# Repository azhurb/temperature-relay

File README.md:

# Smart outlet

Outlet controlled by a temperature sensor using *ATmega8-P*.  
The heater can be connected to the smart outlet and it will act as a thermostat.

## Demo

## License
Licensed under the MIT license.

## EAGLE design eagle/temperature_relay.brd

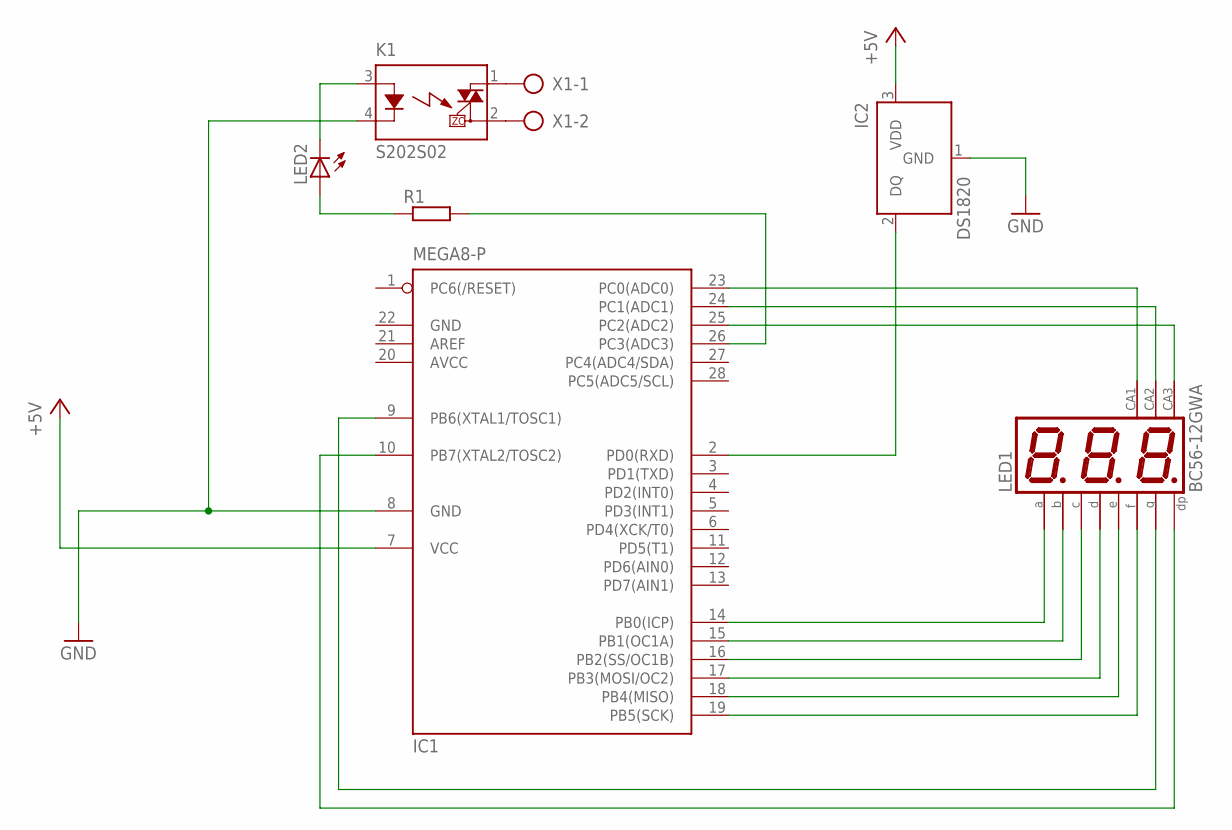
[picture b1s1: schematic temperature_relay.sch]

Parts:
IC1: MEGA8-P; DIL28-3
IC2: DS1820; TO-92
K1: S202S02
LED1: BC56-12GWA; BX56-12
LED2: LED5MM
R1: R-EU_0309/12; 0309/12
X1: AK300/2

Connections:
+5V: IC1.7 (VCC), IC2.3 (VDD)
AVCC: IC1.20 (AVCC)
GND: IC1.8 (GND), IC1.22 (GND), IC2.1 (GND), K1.4 (K)
unnamed: IC1.23 (PC0(ADC0)), LED1.12 (CA)
unnamed: IC1.24 (PC1(ADC1)), LED1.9 (CA)
unnamed: IC1.25 (PC2(ADC2)), LED1.8 (CA)
unnamed: IC1.14 (PB0(ICP)), LED1.11 (A)
unnamed: IC1.15 (PB1(OC1A)), LED1.7 (B)
unnamed: IC1.16 (PB2(SS/OC1B)), LED1.4 (C)
unnamed: IC1.17 (PB3(MOSI/OC2)), LED1.2 (D)
unnamed: IC1.18 (PB4(MISO)), LED1.1 (E)
unnamed: IC1.19 (PB5(SCK)), LED1.10 (F)
unnamed: IC1.9 (PB6(XTAL1/TOSC1)), LED1.5 (G)
unnamed: IC1.10 (PB7(XTAL2/TOSC2)), LED1.3 (DP)
unnamed: IC1.2 (PD0(RXD)), IC2.2 (DQ)
unnamed: IC1.26 (PC3(ADC3)), R1.2
unnamed: LED2.A, R1.1
unnamed: K1.3 (A), LED2.K (C)
unnamed: K1.2 (DS2), X1.2
unnamed: K1.1 (DS1), X1.1

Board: 2 copper layers, 7 parts (0 on the bottom side), 19 nets, no tracks yet.

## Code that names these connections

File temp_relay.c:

/***Использование динамической индикации***/
#include <avr/io.h>
#include <avr/interrupt.h>
#include <util/delay.h>

#include "delay.h"
#include "onewire.h"
#include "ds18x20.h"


char SEGMENT[ ] = {0x3F, 0x06, 0x5B, 0x4F, 0x66, 0x6D, 0x7D, 0x07, 0x7F, 0x6F};

volatile unsigned char segcounter = 0;
volatile int display1 = 0;

// Обработчик прерывания по переполнению таймера2
ISR (TIMER2_OVF_vect)
{    
	PORTB = 0x00; //гасим все разряды
	DDRC  = (1 << segcounter) | (PORTC & (1 << PC3)); //выбираем следующий разряд
	switch (segcounter)
	{     
		case 0:
			PORTB = SEGMENT[display1 % 1000 / 100]; // здесь раскладываем число на разряды
			break;
			case 1:
			PORTB = SEGMENT[display1 % 100 / 10] | 0x80;
			break;    
			case 2:
			PORTB = SEGMENT[display1 % 10];
			break;
		}
		if ((segcounter++) > 1) segcounter = 0;    
	}

unsigned char	nDevices;	// количество сенсоров
unsigned char	owDevicesIDs[MAXDEVICES][8];	// Их ID

unsigned char search_ow_devices(void) // поиск всех устройств на шине
{ 
	unsigned char	i;
	unsigned char	id[OW_ROMCODE_SIZE];
	unsigned char	diff, sensors_count;

	sensors_count = 0;

	for( diff = OW_SEARCH_FIRST; diff != OW_LAST_DEVICE && sensors_count < MAXDEVICES ; )
	{ 
		OW_FindROM( &diff, &id[0] );

		if( diff == OW_PRESENCE_ERR ) break;

		if( diff == OW_DATA_ERR )	break;

		for (i=0;i<OW_ROMCODE_SIZE;i++)
			owDevicesIDs[sensors_count][i] = id[i];

		sensors_count++;
	}
	return sensors_count;
}


/***Главная функция***/
int main (void) 
{
	DDRB |= (1 << PB6)|(1 << PB5)|(1 << PB4)|(1 << PB3)|(1 << PB2)|(1 << PB1)|(1 << PB0);
	DDRC |= (1 << PC3)|(1 << PC2)|(1 << PC1)|(1 << PC0);
	PORTB = 0x00;

	DDRD = 0b00000010; PORTD = 0b00000000;

	TIMSK |= (1 << TOIE2); // разрешение прерывания по таймеру2
	TCCR2 |= (1 << CS21); //предделитель на 8

	sei(); //глобально разрешаем прерывания

	timerDelayInit();

	nDevices = search_ow_devices(); // ищем все устройства

	unsigned char	data[2]; // переменная для хранения старшего и младшего байта данных
	char readResult;
	unsigned char	themperature[3]; // в этот массив будет записана температура

	while(1)
	{
		
		for (unsigned char i=0; i<nDevices; i++)
		{
			
			switch (owDevicesIDs[i][0])
			{

				case OW_DS18B20_FAMILY_CODE: { // если найден термодатчик DS18B20

					DS18x20_StartMeasureAddressed(owDevicesIDs[i]); // запускаем измерение
					timerDelayMs(800); // ждем минимум 750 мс, пока конвентируется температура

					readResult = DS18x20_ReadData(owDevicesIDs[i], data);

					if (readResult == 1){
						DS18x20_ConvertToThemperature(data, themperature); // преобразовываем температуру в человекопонятный вид

						display1 = themperature[1]*10 + themperature[2]/10;

						if (display1 < 200){
							PORTC |= (1 << PC3);
						}else if (display1 > 220){
							PORTC &= ~(1 << PC3);
						}
					}

				} break;
			}
		}
	}
}

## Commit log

2013-09-07 init
2013-09-08 1-wire working?
2013-09-09 temperature bug
2013-09-10 finally working ds18b20!
2013-09-11 Working relay!
2013-09-12 added eagle files
2013-09-18 changed temperature borders
2018-04-18 Add youtube cover
2018-04-18 Fix youtube link
2018-07-27 Fix comments encoding
2018-07-28 Fix formatting
2018-07-30 Create LICENSE
